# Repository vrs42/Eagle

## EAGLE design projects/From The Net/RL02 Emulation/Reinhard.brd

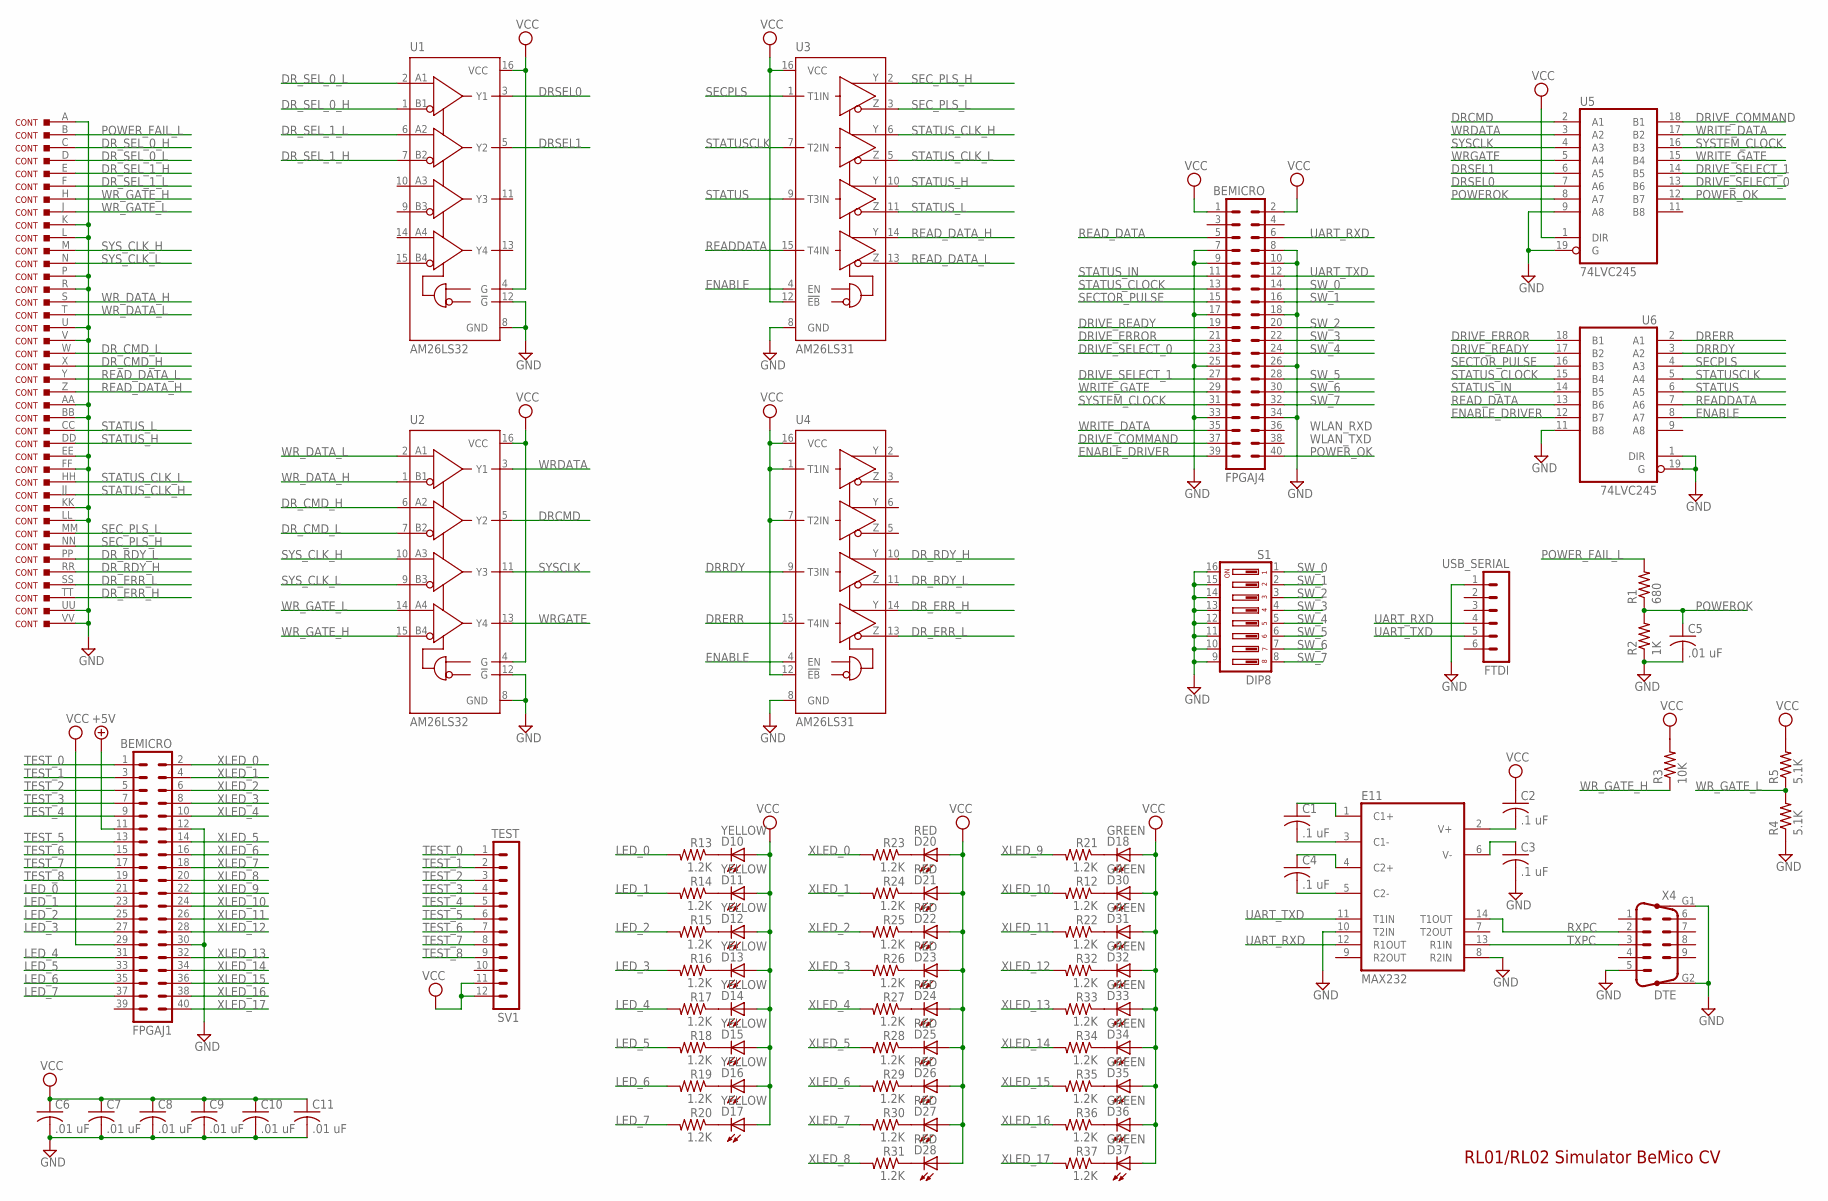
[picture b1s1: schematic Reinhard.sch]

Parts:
C1, C2, C3, C4: .1 uF; C050-025X075
C5, C6, C7, C8, C9, C10, C11: .01 uF; C050-025X075
CONT: DEC40PINSV; DEC40PINV
D10, D11, D12, D13, D14, D15, D16, D17: YELLOW; LED3MM
D18, D30, D31, D32, D33, D34, D35, D36, D37: GREEN; LED3MM
D20, D21, D22, D23, D24, D25, D26, D27, D28: RED; LED3MM
E11: MAX232; DIL16
FPGAJ1, FPGAJ4: BEMICRO; MA20-2
FTDI: USB_SERIAL; MA06-1
R1: 680; 0207/10
R2: 1K; 0207/10
R3: 10K; 0207/10
R4, R5: 5.1K; 0207/10
R12, R13, R14, R15, R16, R17, R18, R19, R20, R21, R22, R23, R24, R25, R26, R27, R28, R29, R30, R31, R32, R33, R34, R35, R36, R37: 1.2K; 0207/10
S1: DIP8; DIP08YL
SV1: TEST; MA12-1
U1, U2: AM26LS32; DIL16
U3, U4: AM26LS31; DIL16
U5, U6: 74LVC245; DIL20
X4: DTE; M09HP

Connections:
+5V: FPGAJ1.11
DRCMD: U2.5 (Y2), U5.2 (A1)
DRERR: U4.15 (T4IN), U6.2 (A1)
DRIVE_COMMAND: FPGAJ4.37, U5.18 (B1)
DRIVE_ERROR: FPGAJ4.21, U6.18 (B1)
DRIVE_READY: FPGAJ4.19, U6.17 (B2)
DRIVE_SELECT_0: FPGAJ4.23, U5.13 (B6)
DRIVE_SELECT_1: FPGAJ4.27, U5.14 (B5)
DRRDY: U4.9 (T3IN), U6.3 (A2)
DRSEL0: U1.3 (Y1), U5.7 (A6)
DRSEL1: U1.5 (Y2), U5.6 (A5)
DR_CMD_H: CONT.X, U2.6 (A2)
DR_CMD_L: CONT.W, U2.7 (B2)
DR_ERR_H: CONT.TT, U4.14 (Y4)
DR_ERR_L: CONT.SS, U4.13 (Z4)
DR_RDY_H: CONT.RR, U4.10 (Y3)
DR_RDY_L: CONT.PP, U4.11 (Z3)
DR_SEL_0_H: CONT.C, U1.1 (B1)
DR_SEL_0_L: CONT.D, U1.2 (A1)
DR_SEL_1_H: CONT.E, U1.7 (B2)
DR_SEL_1_L: CONT.F, U1.6 (A2)
ENABLE: U3.4 (EN), U4.4 (EN), U6.8 (A7)
ENABLE_DRIVER: FPGAJ4.39, U6.12 (B7)
GND: C3.2, C5.2, C6.2, C7.2, C8.2, C9.2, C10.2, C11.2, CONT.A, CONT.AA, CONT.BB, CONT.EE, CONT.FF, CONT.K, CONT.KK, CONT.L, CONT.LL, CONT.P, CONT.R, CONT.U, CONT.UU, CONT.V, CONT.VV, E11.8 (R2IN), E11.10 (T2IN), E11.15 (GND), FPGAJ1.12, FPGAJ1.30, FPGAJ4.7, FPGAJ4.8, FPGAJ4.9, FPGAJ4.10, FPGAJ4.17, FPGAJ4.18, FPGAJ4.25, FPGAJ4.26, FPGAJ4.33, FPGAJ4.34, FTDI.1, R2.1, R4.1, S1.9, S1.10, S1.11, S1.12, S1.13, S1.14, S1.15, S1.16, U1.8 (GND), U1.12 (!G), U2.8 (GND), U2.12 (!G), U3.8 (GND), U4.8 (GND), U5.9 (A8), U5.10 (GND), U5.19 (G), U6.1 (DIR), U6.10 (GND), U6.11 (B8), U6.19 (G), X4.5, X4.G1, X4.G2
LED_0: FPGAJ1.21, R13.2
LED_1: FPGAJ1.23, R14.2
LED_2: FPGAJ1.25, R15.2
LED_3: FPGAJ1.27, R16.2
LED_4: FPGAJ1.31, R17.2
LED_5: FPGAJ1.33, R18.2
LED_6: FPGAJ1.35, R19.2
LED_7: FPGAJ1.37, R20.2
unnamed: C1.2, E11.3 (C1-)
unnamed: C1.1, E11.1 (C1+)
unnamed: C4.1, E11.4 (C2+)
unnamed: C4.2, E11.5 (C2-)
unnamed: C3.1, E11.6 (V-)
unnamed: C2.2, E11.2 (V+)
unnamed: D30.K (C), R12.1
unnamed: D31.K (C), R22.1
unnamed: D32.K (C), R32.1
unnamed: D33.K (C), R33.1
unnamed: D34.K (C), R34.1
unnamed: D35.K (C), R35.1
unnamed: D36.K (C), R36.1
unnamed: D37.K (C), R37.1
unnamed: D10.K (C), R13.1
unnamed: D11.K (C), R14.1
unnamed: D12.K (C), R15.1
unnamed: D13.K (C), R16.1
unnamed: D14.K (C), R17.1
unnamed: D15.K (C), R18.1
unnamed: D16.K (C), R19.1
unnamed: D17.K (C), R20.1
unnamed: D18.K (C), R21.1
unnamed: D20.K (C), R23.1
unnamed: D21.K (C), R24.1
unnamed: D22.K (C), R25.1
unnamed: D23.K (C), R26.1
unnamed: D24.K (C), R27.1
unnamed: D25.K (C), R28.1
unnamed: D26.K (C), R29.1
unnamed: D27.K (C), R30.1
unnamed: D28.K (C), R31.1
POWEROK: C5.1, R1.1, R2.2, U5.8 (A7)
POWER_FAIL_L: CONT.B, R1.2
POWER_OK: FPGAJ4.40, U5.12 (B7)
READDATA: U3.15 (T4IN), U6.7 (A6)
READ_DATA: FPGAJ4.5, U6.13 (B6)
READ_DATA_H: CONT.Z, U3.14 (Y4)
READ_DATA_L: CONT.Y, U3.13 (Z4)
RXPC: E11.14 (T1OUT), X4.2
SECPLS: U3.1 (T1IN), U6.4 (A3)
SECTOR_PULSE: FPGAJ4.15, U6.16 (B3)
SEC_PLS_H: CONT.NN, U3.2 (Y1)
SEC_PLS_L: CONT.MM, U3.3 (Z1)
STATUS: U3.9 (T3IN), U6.6 (A5)
STATUSCLK: U3.7 (T2IN), U6.5 (A4)
STATUS_CLK_H: CONT.JJ, U3.6 (Y2)
STATUS_CLK_L: CONT.HH, U3.5 (Z2)
STATUS_CLOCK: FPGAJ4.13, U6.15 (B4)
STATUS_H: CONT.DD, U3.10 (Y3)
STATUS_IN: FPGAJ4.11, U6.14 (B5)
STATUS_L: CONT.CC, U3.11 (Z3)
SW_0: FPGAJ4.14, S1.1
SW_1: FPGAJ4.16, S1.2
SW_2: FPGAJ4.20, S1.3
SW_3: FPGAJ4.22, S1.4
SW_4: FPGAJ4.24, S1.5
SW_5: FPGAJ4.28, S1.6
SW_6: FPGAJ4.30, S1.7
SW_7: FPGAJ4.32, S1.8
SYSCLK: U2.11 (Y3), U5.4 (A3)
SYSTEM_CLOCK: FPGAJ4.31, U5.16 (B3)
SYS_CLK_H: CONT.M, U2.10 (A3)
SYS_CLK_L: CONT.N, U2.9 (B3)
TEST_0: FPGAJ1.1, SV1.1
TEST_1: FPGAJ1.3, SV1.2
TEST_2: FPGAJ1.5, SV1.3
TEST_3: FPGAJ1.7, SV1.4
TEST_4: FPGAJ1.9, SV1.5
TEST_5: FPGAJ1.13, SV1.6
TEST_6: FPGAJ1.15, SV1.7
TEST_7: FPGAJ1.17, SV1.8
TEST_8: FPGAJ1.19, SV1.9
TXPC: E11.13 (R1IN), X4.3
UART_RXD: E11.12 (R1OUT), FPGAJ4.6, FTDI.4
UART_TXD: E11.11 (T1IN), FPGAJ4.12, FTDI.5
VCC: C2.1, C6.1, C7.1, C8.1, C9.1, C10.1, C11.1, D10.A, D11.A, D12.A, D13.A, D14.A, D15.A, D16.A, D17.A, D18.A, D20.A, D21.A, D22.A, D23.A, D24.A, D25.A, D26.A, D27.A, D28.A, D30.A, D31.A, D32.A, D33.A, D34.A, D35.A, D36.A, D37.A, E11.16 (VCC), FPGAJ1.29, FPGAJ4.1, FPGAJ4.2, R3.2, R5.2, SV1.11, SV1.12, U1.4 (G), U1.16 (VCC), U2.4 (G), U2.16 (VCC), U3.12 (!EB), U3.16 (VCC), U4.1 (T1IN), U4.7 (T2IN), U4.12 (!EB), U4.16 (VCC), U5.1 (DIR), U5.20 (VCC), U6.20 (VCC)
WRDATA: U2.3 (Y1), U5.3 (A2)
WRGATE: U2.13 (Y4), U5.5 (A4)
WRITE_DATA: FPGAJ4.35, U5.17 (B2)
WRITE_GATE: FPGAJ4.29, U5.15 (B4)
WR_DATA_H: CONT.S, U2.1 (B1)
WR_DATA_L: CONT.T, U2.2 (A1)
WR_GATE_H: CONT.H, R3.1, U2.15 (B4)
WR_GATE_L: CONT.J, R4.2, R5.1, U2.14 (A4)
XLED_0: FPGAJ1.2, R23.2
XLED_1: FPGAJ1.4, R24.2
XLED_2: FPGAJ1.6, R25.2
XLED_3: FPGAJ1.8, R26.2
XLED_4: FPGAJ1.10, R27.2
XLED_5: FPGAJ1.14, R28.2
XLED_6: FPGAJ1.16, R29.2
XLED_7: FPGAJ1.18, R30.2
XLED_8: FPGAJ1.20, R31.2
XLED_9: FPGAJ1.22, R21.2
XLED_10: FPGAJ1.24, R12.2
XLED_11: FPGAJ1.26, R22.2
XLED_12: FPGAJ1.28, R32.2
XLED_13: FPGAJ1.32, R33.2
XLED_14: FPGAJ1.34, R34.2
XLED_15: FPGAJ1.36, R35.2
XLED_16: FPGAJ1.38, R36.2
XLED_17: FPGAJ1.40, R37.2

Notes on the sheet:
WLAN_RXD
WLAN_TXD
RL01/RL02 Simulator BeMico CV

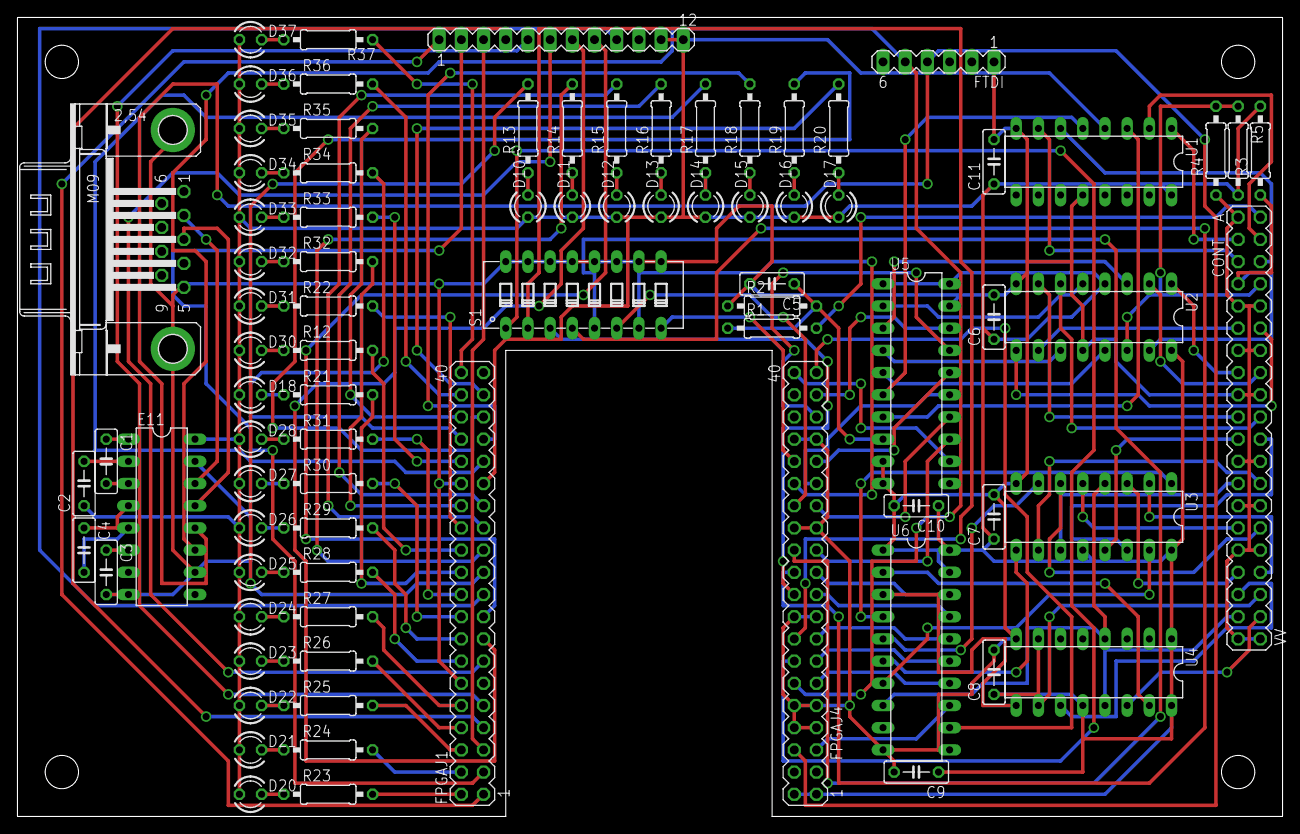
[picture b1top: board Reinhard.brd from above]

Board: 2 copper layers, 144.8 x 91.4 mm, 82 parts (0 on the bottom side), 134 nets.

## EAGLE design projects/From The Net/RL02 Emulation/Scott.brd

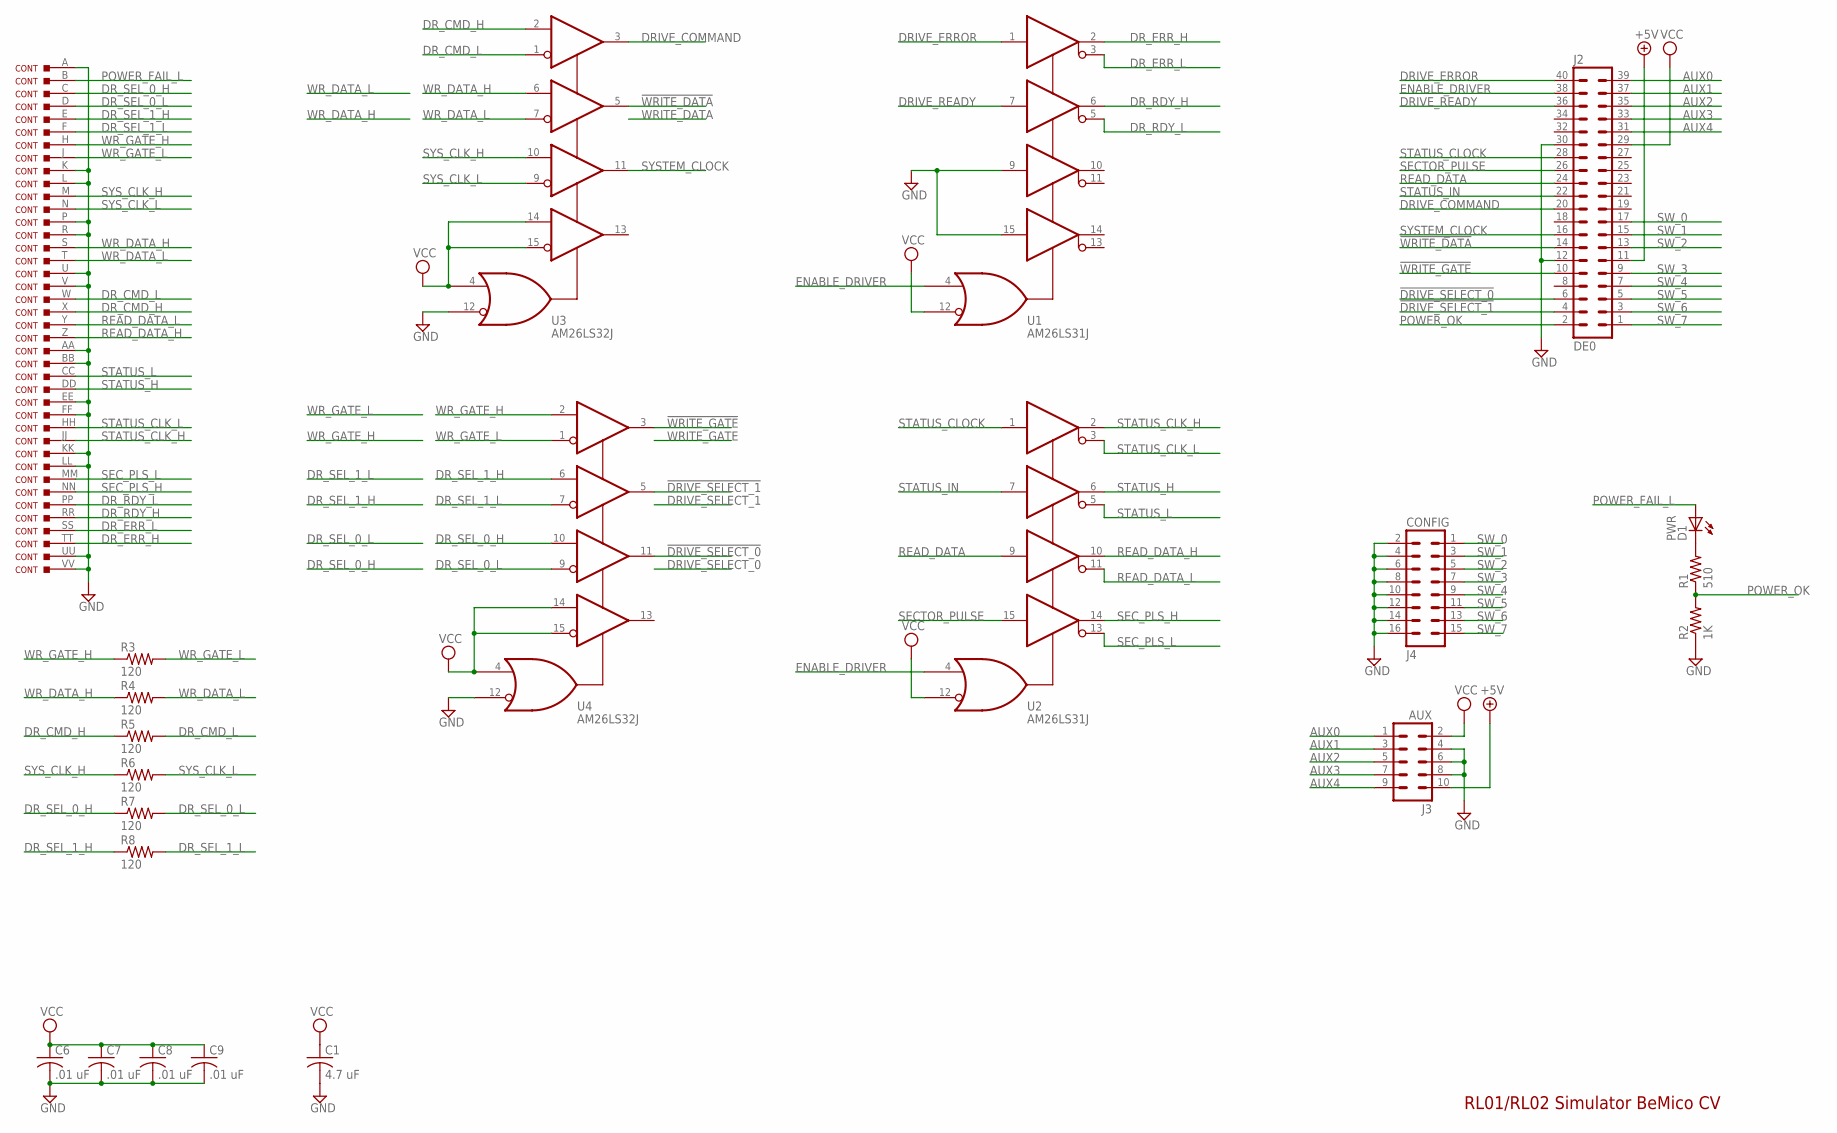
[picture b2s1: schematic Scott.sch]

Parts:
C1: 4.7 uF; C1210K
C6, C7, C8, C9: .01 uF; C0805
CONT: DEC40PINSV; DEC40PINV
D1: PWR; SML0805
J2: DE0; MA20-2
J3: AUX; MA05-2
J4: CONFIG; MA08-2
R1: 510; M0805
R2: 1K; M0805
R3, R4, R5, R6, R7, R8: 120; 0204V
U1, U2: AM26LS31J; SO16
U3, U4: AM26LS32J; SO16

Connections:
!DRIVE_SELECT_0: J2.6, U4.11 (Y3)
!DRIVE_SELECT_1: J2.4, U4.5 (Y2)
!WRITE_DATA: J2.14, U3.5 (Y2)
!WRITE_GATE: J2.10, U4.3 (Y1)
+5V: J2.11, J3.10
AUX0: J2.39, J3.1
AUX1: J2.37, J3.3
AUX2: J2.35, J3.5
AUX3: J2.33, J3.7
AUX4: J2.31, J3.9
DRIVE_COMMAND: J2.20, U3.3 (Y1)
DRIVE_ERROR: J2.40, U1.1 (A1)
DRIVE_READY: J2.36, U1.7 (A2)
DR_CMD_H: CONT.X, R5.1, U3.2 (P1)
DR_CMD_L: CONT.W, R5.2, U3.1 (N1)
DR_ERR_H: CONT.TT, U1.2 (Y1)
DR_ERR_L: CONT.SS, U1.3 (Z1)
DR_RDY_H: CONT.RR, U1.6 (Y2)
DR_RDY_L: CONT.PP, U1.5 (Z2)
DR_SEL_0_H: CONT.C, R7.1, U4.10 (P3)
DR_SEL_0_L: CONT.D, R7.2, U4.9 (N3)
DR_SEL_1_H: CONT.E, R8.1, U4.6 (P2)
DR_SEL_1_L: CONT.F, R8.2, U4.7 (N2)
ENABLE_DRIVER: J2.38, U1.4 (G), U2.4 (G)
GND: C1.2, C6.2, C7.2, C8.2, C9.2, CONT.A, CONT.AA, CONT.BB, CONT.EE, CONT.FF, CONT.K, CONT.KK, CONT.L, CONT.LL, CONT.P, CONT.R, CONT.U, CONT.UU, CONT.V, CONT.VV, J2.12, J2.30, J3.4, J3.6, J3.8, J4.2, J4.4, J4.6, J4.8, J4.10, J4.12, J4.14, J4.16, R2.1, U1.8 (GND), U1.9 (A3), U1.15 (A4), U2.8 (GND), U3.8 (GND), U3.12 (!G), U4.8 (GND), U4.12 (!G)
unnamed: D1.C, R1.2
POWER_FAIL_L: CONT.B, D1.A
POWER_OK: J2.2, R1.1, R2.2
READ_DATA: J2.24, U2.9 (A3)
READ_DATA_H: CONT.Z, U2.10 (Y3)
READ_DATA_L: CONT.Y, U2.11 (Z3)
SECTOR_PULSE: J2.26, U2.15 (A4)
SEC_PLS_H: CONT.NN, U2.14 (Y4)
SEC_PLS_L: CONT.MM, U2.13 (Z4)
STATUS_CLK_H: CONT.JJ, U2.2 (Y1)
STATUS_CLK_L: CONT.HH, U2.3 (Z1)
STATUS_CLOCK: J2.28, U2.1 (A1)
STATUS_H: CONT.DD, U2.6 (Y2)
STATUS_IN: J2.22, U2.7 (A2)
STATUS_L: CONT.CC, U2.5 (Z2)
SW_0: J2.17, J4.1
SW_1: J2.15, J4.3
SW_2: J2.13, J4.5
SW_3: J2.9, J4.7
SW_4: J2.7, J4.9
SW_5: J2.5, J4.11
SW_6: J2.3, J4.13
SW_7: J2.1, J4.15
SYSTEM_CLOCK: J2.16, U3.11 (Y3)
SYS_CLK_H: CONT.M, R6.1, U3.10 (P3)
SYS_CLK_L: CONT.N, R6.2, U3.9 (N3)
VCC: C1.1, C6.1, C7.1, C8.1, C9.1, J2.29, J3.2, U1.12 (!G), U1.16 (VCC), U2.12 (!G), U2.16 (VCC), U3.4 (G), U3.14 (P4), U3.15 (N4), U3.16 (VCC), U4.4 (G), U4.14 (P4), U4.15 (N4), U4.16 (VCC)
WR_DATA_H: CONT.S, R4.1, U3.6 (P2)
WR_DATA_L: CONT.T, R4.2, U3.7 (N2)
WR_GATE_H: CONT.H, R3.1, U4.2 (P1)
WR_GATE_L: CONT.J, R3.2, U4.1 (N1)

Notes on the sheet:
RL01/RL02 Simulator BeMico CV

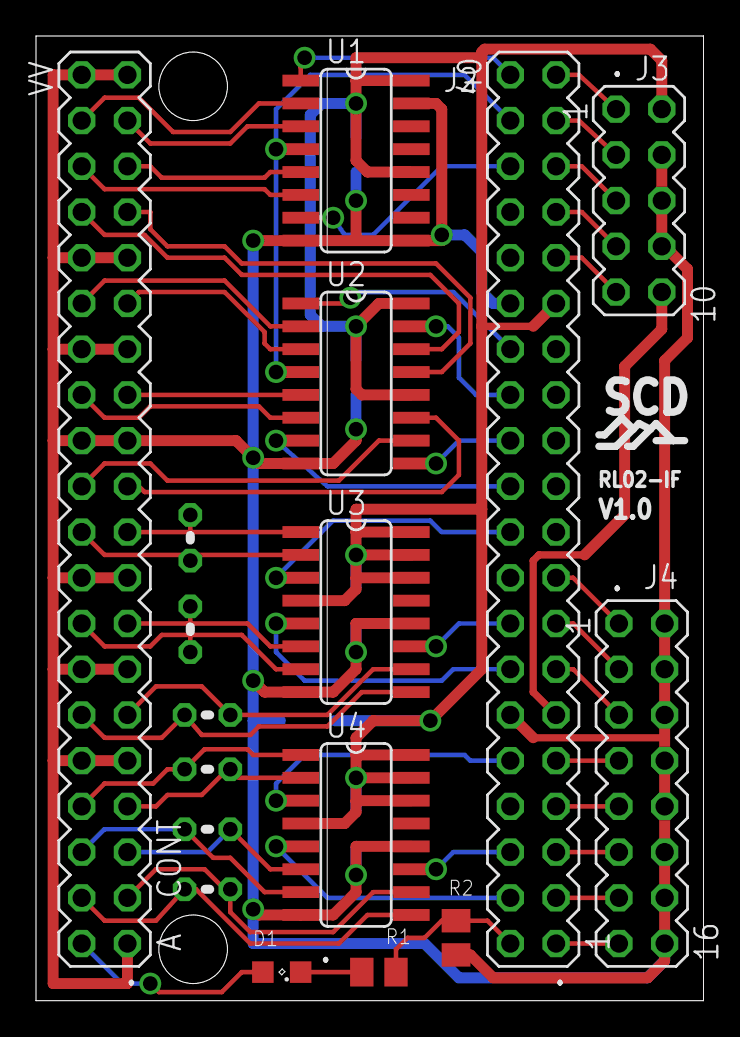
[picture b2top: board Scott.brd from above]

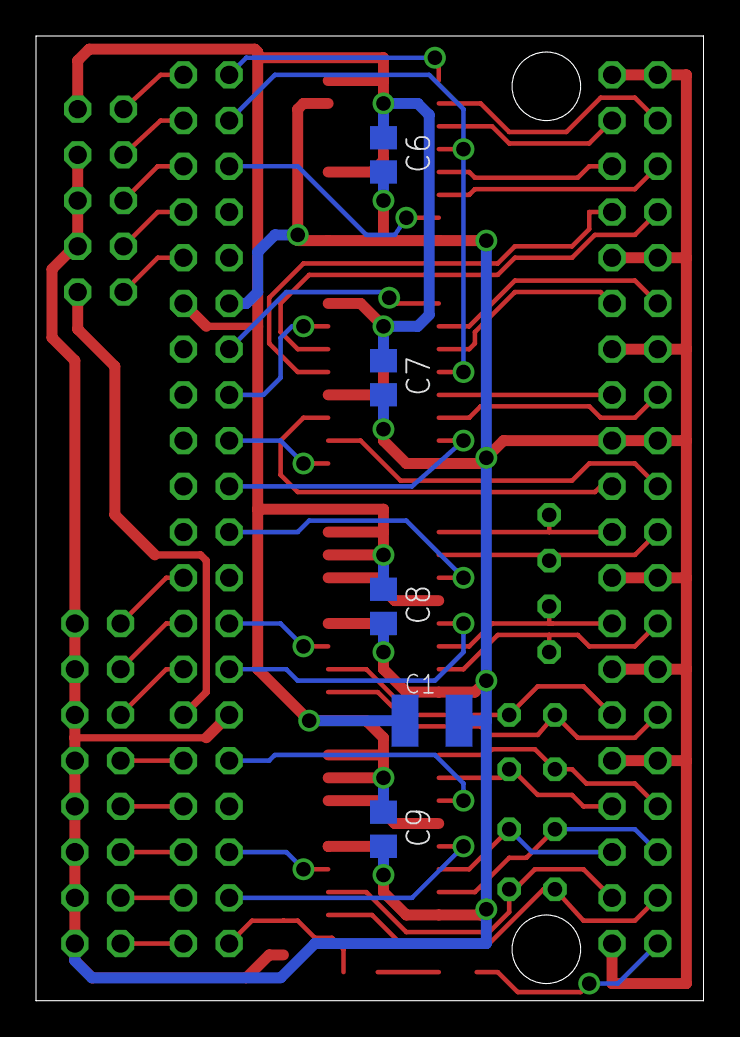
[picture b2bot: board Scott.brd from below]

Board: 2 copper layers, 37.1 x 53.6 mm, 22 parts (5 on the bottom side), 56 nets.

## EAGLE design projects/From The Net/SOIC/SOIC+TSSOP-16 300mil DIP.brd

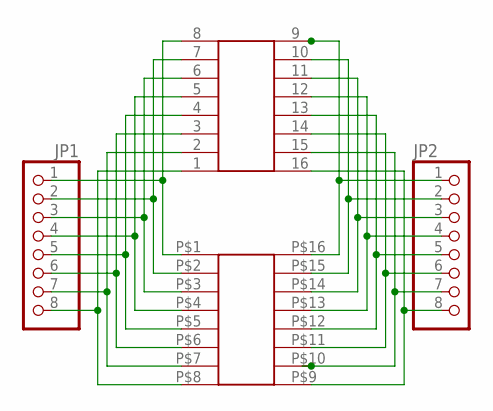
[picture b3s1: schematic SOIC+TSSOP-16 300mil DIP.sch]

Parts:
JP1, JP2: PINHD-1X8; 1X08
U$1: SMD-16SOIC; SO-16NMW
U$2: SMD-16TSSOP; TSSOP-16NM

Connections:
unnamed: JP1.1, U$1.P$1, U$2.8
unnamed: JP1.2, U$1.P$2, U$2.7
unnamed: JP1.3, U$1.P$3, U$2.6
unnamed: JP1.4, U$1.P$4, U$2.5
unnamed: JP1.5, U$1.P$5, U$2.4
unnamed: JP1.6, U$1.P$6, U$2.3
unnamed: JP1.7, U$1.P$7, U$2.2
unnamed: JP1.8, U$1.P$8, U$2.1
unnamed: JP2.1, U$1.P$16, U$2.9
unnamed: JP2.2, U$1.P$15, U$2.10
unnamed: JP2.3, U$1.P$14, U$2.11
unnamed: JP2.4, U$1.P$13, U$2.12
unnamed: JP2.5, U$1.P$12, U$2.13
unnamed: JP2.6, U$1.P$11, U$2.14
unnamed: JP2.7, U$1.P$10, U$2.15
unnamed: JP2.8, U$1.P$9, U$2.16

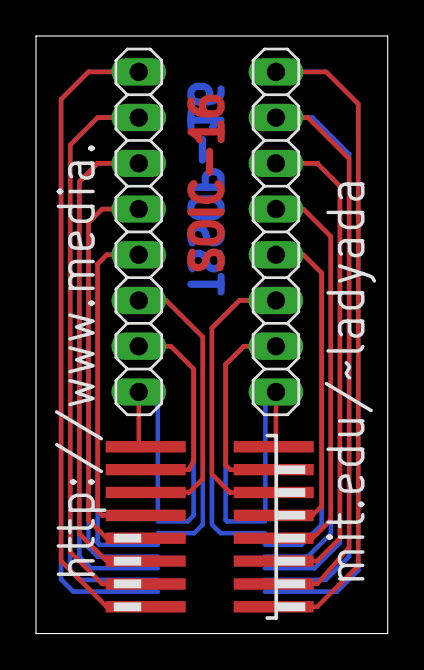
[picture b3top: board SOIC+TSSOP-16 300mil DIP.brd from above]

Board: 2 copper layers, 19.5 x 33.2 mm, 4 parts (1 on the bottom side), 16 nets.

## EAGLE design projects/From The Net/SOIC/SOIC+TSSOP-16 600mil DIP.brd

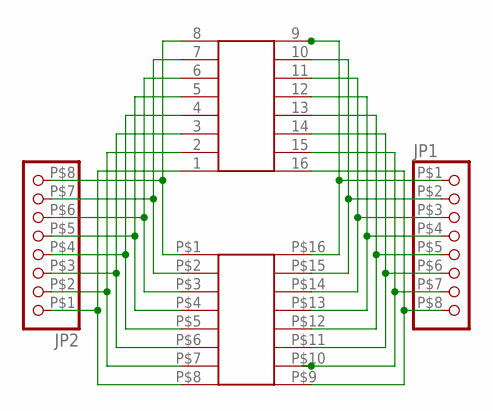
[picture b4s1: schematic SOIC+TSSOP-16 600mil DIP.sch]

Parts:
JP1, JP2: PINHD-1X8THIN; HEADER1X8
U$1: SMD-16SOIC; SO-16NMW
U$2: SMD-16TSSOP; TSSOP-16NM

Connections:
unnamed: JP2.P$8 (8), U$1.P$1, U$2.8
unnamed: JP2.P$7 (7), U$1.P$2, U$2.7
unnamed: JP2.P$6 (6), U$1.P$3, U$2.6
unnamed: JP2.P$5 (5), U$1.P$4, U$2.5
unnamed: JP2.P$4 (4), U$1.P$5, U$2.4
unnamed: JP2.P$3 (3), U$1.P$6, U$2.3
unnamed: JP2.P$2 (2), U$1.P$7, U$2.2
unnamed: JP2.P$1 (1), U$1.P$8, U$2.1
unnamed: JP1.P$1 (1), U$1.P$16, U$2.9
unnamed: JP1.P$2 (2), U$1.P$15, U$2.10
unnamed: JP1.P$3 (3), U$1.P$14, U$2.11
unnamed: JP1.P$4 (4), U$1.P$13, U$2.12
unnamed: JP1.P$5 (5), U$1.P$12, U$2.13
unnamed: JP1.P$6 (6), U$1.P$11, U$2.14
unnamed: JP1.P$7 (7), U$1.P$10, U$2.15
unnamed: JP1.P$8 (8), U$1.P$9, U$2.16

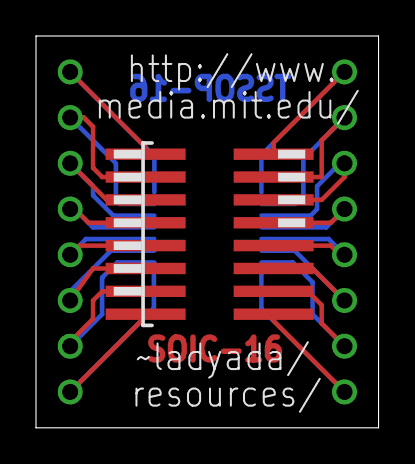
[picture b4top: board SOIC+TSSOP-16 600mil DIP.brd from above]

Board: 2 copper layers, 19.0 x 21.8 mm, 4 parts (1 on the bottom side), 16 nets.

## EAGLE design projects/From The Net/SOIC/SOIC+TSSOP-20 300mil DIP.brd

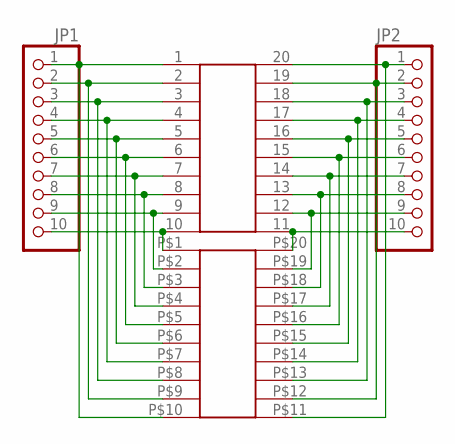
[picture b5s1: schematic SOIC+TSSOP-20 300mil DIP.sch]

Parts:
JP1, JP2: PINHD-1X10; 1X10
U$1: SMD-20TSSOP; TSSOP-20NM
U$2: SMD-20SOIC; SO-20NMW

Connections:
unnamed: JP1.1, U$1.1, U$2.P$10
unnamed: JP1.2, U$1.2, U$2.P$9
unnamed: JP1.3, U$1.3, U$2.P$8
unnamed: JP1.4, U$1.4, U$2.P$7
unnamed: JP1.5, U$1.5, U$2.P$6
unnamed: JP1.6, U$1.6, U$2.P$5
unnamed: JP1.7, U$1.7, U$2.P$4
unnamed: JP1.8, U$1.8, U$2.P$3
unnamed: JP1.9, U$1.9, U$2.P$2
unnamed: JP1.10, U$1.10, U$2.P$1
unnamed: JP2.1, U$1.20, U$2.P$11
unnamed: JP2.2, U$1.19, U$2.P$12
unnamed: JP2.3, U$1.18, U$2.P$13
unnamed: JP2.5, U$1.16, U$2.P$15
unnamed: JP2.4, U$1.17, U$2.P$14
unnamed: JP2.6, U$1.15, U$2.P$16
unnamed: JP2.7, U$1.14, U$2.P$17
unnamed: JP2.8, U$1.13, U$2.P$18
unnamed: JP2.9, U$1.12, U$2.P$19
unnamed: JP2.10, U$1.11, U$2.P$20

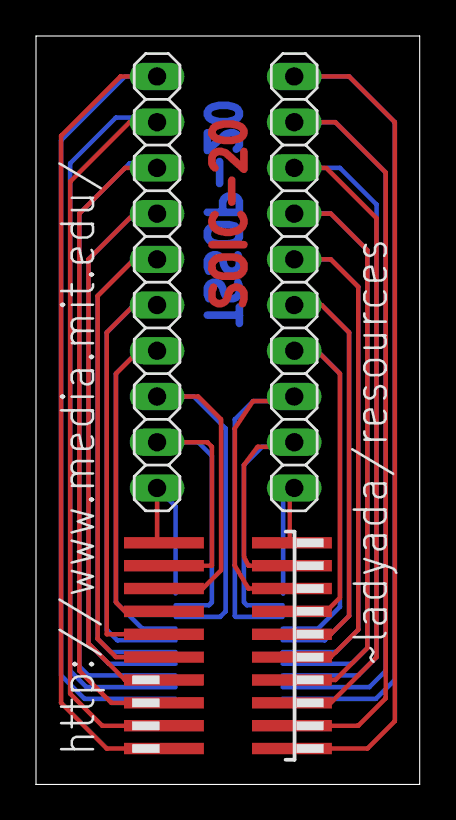
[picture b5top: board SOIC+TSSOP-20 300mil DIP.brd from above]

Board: 2 copper layers, 21.3 x 41.6 mm, 4 parts (1 on the bottom side), 20 nets.

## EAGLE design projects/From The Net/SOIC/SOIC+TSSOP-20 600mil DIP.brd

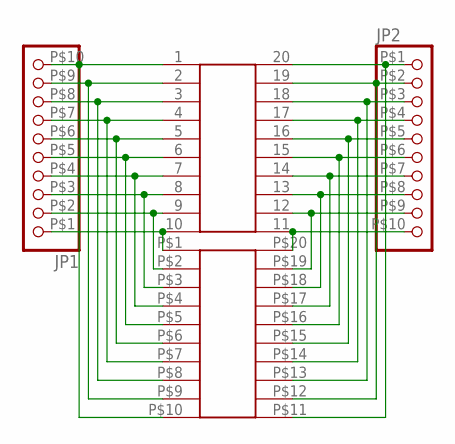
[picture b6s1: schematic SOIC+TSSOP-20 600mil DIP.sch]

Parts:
JP1, JP2: PINHD-1X10THIN; HEADER1X10
U$1: SMD-20TSSOP; TSSOP-20NM
U$2: SMD-20SOIC; SO-20NMW

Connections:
unnamed: JP1.P$10 (10), U$1.1, U$2.P$10
unnamed: JP1.P$9 (9), U$1.2, U$2.P$9
unnamed: JP1.P$8 (8), U$1.3, U$2.P$8
unnamed: JP1.P$7 (7), U$1.4, U$2.P$7
unnamed: JP1.P$6 (6), U$1.5, U$2.P$6
unnamed: JP1.P$5 (5), U$1.6, U$2.P$5
unnamed: JP1.P$4 (4), U$1.7, U$2.P$4
unnamed: JP1.P$3 (3), U$1.8, U$2.P$3
unnamed: JP1.P$2 (2), U$1.9, U$2.P$2
unnamed: JP1.P$1 (1), U$1.10, U$2.P$1
unnamed: JP2.P$1 (1), U$1.20, U$2.P$11
unnamed: JP2.P$2 (2), U$1.19, U$2.P$12
unnamed: JP2.P$3 (3), U$1.18, U$2.P$13
unnamed: JP2.P$5 (5), U$1.16, U$2.P$15
unnamed: JP2.P$4 (4), U$1.17, U$2.P$14
unnamed: JP2.P$6 (6), U$1.15, U$2.P$16
unnamed: JP2.P$7 (7), U$1.14, U$2.P$17
unnamed: JP2.P$8 (8), U$1.13, U$2.P$18
unnamed: JP2.P$9 (9), U$1.12, U$2.P$19
unnamed: JP2.P$10 (10), U$1.11, U$2.P$20

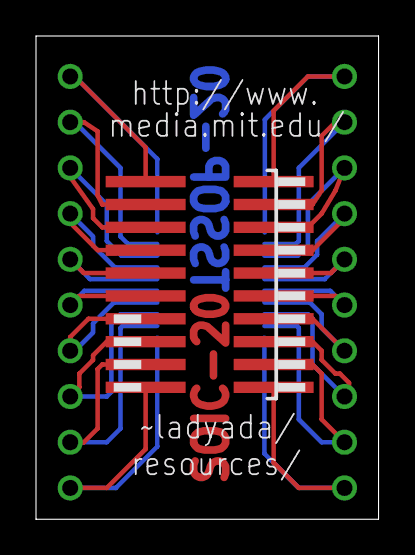
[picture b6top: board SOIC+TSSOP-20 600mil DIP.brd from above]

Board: 2 copper layers, 19.0 x 26.8 mm, 4 parts (1 on the bottom side), 20 nets.

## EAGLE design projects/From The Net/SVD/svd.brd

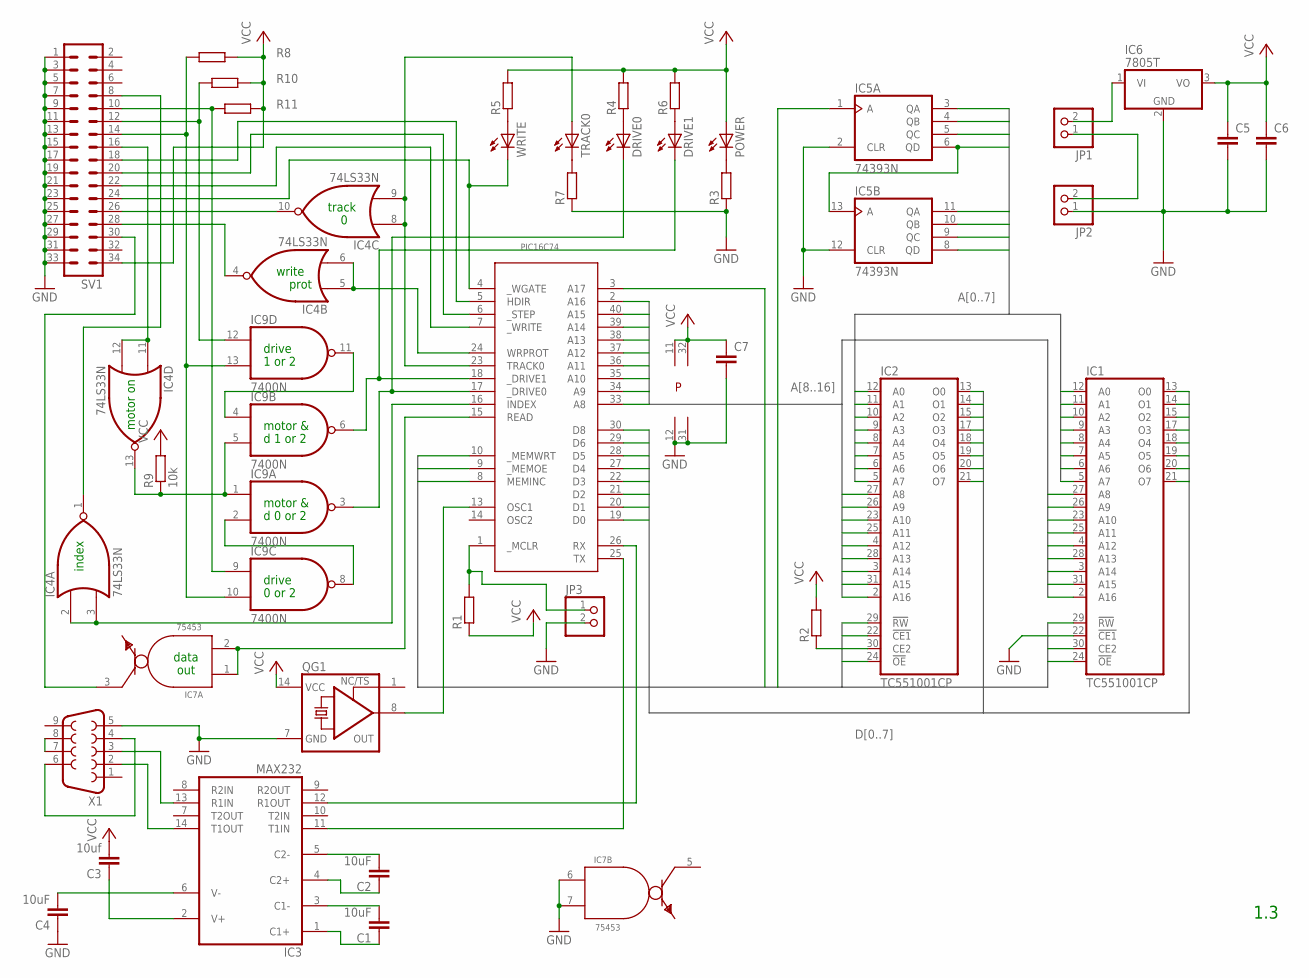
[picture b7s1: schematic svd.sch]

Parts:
C1, C2, C4: 10uF; C2.5-5
C3: 10uf; C2.5-5
C5, C6: C5/5; C5B5
C7: C2,5-3; C2.5-3
DRIVE0, DRIVE1: LED3MM
IC1, IC2: TC551001CP; DIL32
IC3: MAX232; DIL16
IC4: 74LS33N; DIL14
IC5: 74393N; DIL14
IC6: 7805T; TO220H
IC7: 75453; DIL08
IC9: 7400N; DIL14
JP1, JP2, JP3: PINHD-1X2; 1X02
PIC16C74: SVD-PIC16C74; DIL40
POWER: LED3MM
QG1: XO-14; DIL14S
R1, R2, R3, R4, R5, R6, R7, R8, R10, R11: R-EU_0204/5; 0204/5
R9: 10k; 0204/5
SV1: ML34
TRACK0: LED3MM
WRITE: LED3MM
X1: F09HP

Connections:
!OE: IC1.24 (!OE), IC2.24 (!OE), PIC16C74.9 (_MEMOE)
!WE: IC1.29 (!RW), IC2.29 (!RW), PIC16C74.10 (_MEMWRT)
A0: IC1.12 (A0), IC2.12 (A0), IC5.3 (QA)
A1: IC1.11 (A1), IC2.11 (A1), IC5.4 (QB)
A2: IC1.10 (A2), IC2.10 (A2), IC5.5 (QC)
A3: IC1.9 (A3), IC2.9 (A3), IC5.6 (QD), IC5.13 (A)
A4: IC1.8 (A4), IC2.8 (A4), IC5.11 (QA)
A5: IC1.7 (A5), IC2.7 (A5), IC5.10 (QB)
A6: IC1.6 (A6), IC2.6 (A6), IC5.9 (QC)
A7: IC1.5 (A7), IC2.5 (A7), IC5.8 (QD)
A8: IC1.27 (A8), IC2.27 (A8), PIC16C74.33 (A8)
A9: IC1.26 (A9), IC2.26 (A9), PIC16C74.34 (A9)
A10: IC1.23 (A10), IC2.23 (A10), PIC16C74.35 (A10)
A11: IC1.25 (A11), IC2.25 (A11), PIC16C74.36 (A11)
A12: IC1.4 (A12), IC2.4 (A12), PIC16C74.37 (A12)
A13: IC1.28 (A13), IC2.28 (A13), PIC16C74.38 (A13)
A14: IC1.3 (A14), IC2.3 (A14), PIC16C74.39 (A14)
A15: IC1.31 (A15), IC2.31 (A15), PIC16C74.40 (A15)
A16: IC1.2 (A16), IC2.2 (A16), PIC16C74.2 (A16)
A17: IC1.30 (CE2), IC2.22 (!CE1), PIC16C74.3 (A17)
CLK: IC5.1 (A), PIC16C74.8 (MEMINC)
D0: IC1.13 (O0), IC2.13 (O0), PIC16C74.19 (D0)
D1: IC1.14 (O1), IC2.14 (O1), PIC16C74.20 (D1)
D2: IC1.15 (O2), IC2.15 (O2), PIC16C74.21 (D2)
D3: IC1.17 (O3), IC2.17 (O3), PIC16C74.22 (D3)
D4: IC1.18 (O4), IC2.18 (O4), PIC16C74.27 (D4)
D5: IC1.19 (O5), IC2.19 (O5), PIC16C74.28 (D5)
D6: IC1.20 (O6), IC2.20 (O6), PIC16C74.29 (D6)
D7: IC1.21 (O7), IC2.21 (O7), PIC16C74.30 (D8)
GND: C4.1, C5.2, C6.2, C7.2, IC1.16 (GND), IC1.22 (!CE1), IC2.16 (GND), IC3.15 (GND), IC4.7 (GND), IC5.2 (CLR), IC5.7 (GND), IC5.12 (CLR), IC6.2 (GND), IC7.4 (GND), IC7.6 (I0), IC7.7 (I1), IC9.7 (GND), JP2.1, JP3.2, PIC16C74.12 (GND), PIC16C74.31 (GND), QG1.7 (GND), R3.1, R7.1, SV1.1, SV1.3, SV1.5, SV1.7, SV1.9, SV1.11, SV1.13, SV1.15, SV1.17, SV1.19, SV1.21, SV1.23, SV1.25, SV1.27, SV1.29, SV1.31, SV1.33, X1.5
unnamed: IC2.30 (CE2), R2.1
unnamed: JP3.1, PIC16C74.1 (_MCLR), R1.2
unnamed: C1.1, IC3.1 (C1+)
unnamed: C1.2, IC3.3 (C1-)
unnamed: C2.1, IC3.4 (C2+)
unnamed: C2.2, IC3.5 (C2-)
unnamed: C3.1, IC3.2 (V+)
unnamed: PIC16C74.13 (OSC1), QG1.8 (OUT)
unnamed: IC3.12 (R1OUT), PIC16C74.26 (RX)
unnamed: DRIVE1.K (C), IC9.6 (O), PIC16C74.18 (_DRIVE1)
unnamed: IC4.11 (I0), IC4.12 (I1), SV1.16
unnamed: IC9.12 (I0), R10.1, SV1.12
unnamed: IC4.13 (O), IC9.1 (I0), IC9.5 (I1), R9.1
unnamed: IC4.1 (O), SV1.8
unnamed: PIC16C74.4 (_WGATE), SV1.24, WRITE.K (C)
unnamed: PIC16C74.7 (_WRITE), SV1.22
unnamed: IC4.10 (O), SV1.26
unnamed: X1.7, X1.8
unnamed: IC7.1 (I0), IC7.2 (I1), PIC16C74.15 (READ)
unnamed: IC9.4 (I0), IC9.11 (O)
unnamed: IC4.8 (I0), IC4.9 (I1), PIC16C74.23 (TRACK0), TRACK0.A
unnamed: DRIVE0.K (C), IC9.3 (O), PIC16C74.17 (_DRIVE0)
unnamed: IC3.11 (T1IN), PIC16C74.25 (TX)
unnamed: IC3.13 (R1IN), X1.3
unnamed: X1.4, X1.6
unnamed: IC3.14 (T1OUT), X1.2
unnamed: C4.2, IC3.6 (V-)
unnamed: IC4.2 (I0), IC4.3 (I1), PIC16C74.16 (INDEX)
unnamed: IC6.1 (VI), JP1.2
unnamed: POWER.K (C), R3.2
unnamed: DRIVE0.A, R4.1
unnamed: DRIVE1.A, R6.1
unnamed: R5.1, WRITE.A
unnamed: R7.2, TRACK0.K (C)
unnamed: JP1.1, JP2.2
unnamed: IC7.3 (O), SV1.30
unnamed: IC4.5 (I0), IC4.6 (I1), PIC16C74.24 (WRPROT)
unnamed: IC9.9 (I0), R11.1, SV1.10
unnamed: IC9.2 (I1), IC9.8 (O)
unnamed: IC4.4 (O), SV1.28
unnamed: PIC16C74.6 (_STEP), SV1.20
unnamed: PIC16C74.5 (HDIR), SV1.18
unnamed: IC9.10 (I1), IC9.13 (I1), R8.1, SV1.14
VCC: C3.2, C5.1, C6.1, C7.1, IC1.32 (VCC), IC2.32 (VCC), IC3.16 (VCC), IC4.14 (VCC), IC5.14 (VCC), IC6.3 (VO), IC7.8 (VCC), IC9.14 (VCC), PIC16C74.11 (VCC), PIC16C74.32 (VCC), POWER.A, QG1.14 (VCC), R1.1, R2.2, R4.2, R5.2, R6.2, R8.2, R9.2, R10.2, R11.2, SV1.34

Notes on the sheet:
1.3
motor on
index
data
out
write
prot
track
drive
motor &
1 or 2
d 1 or 2
d 0 or 2
0 or 2

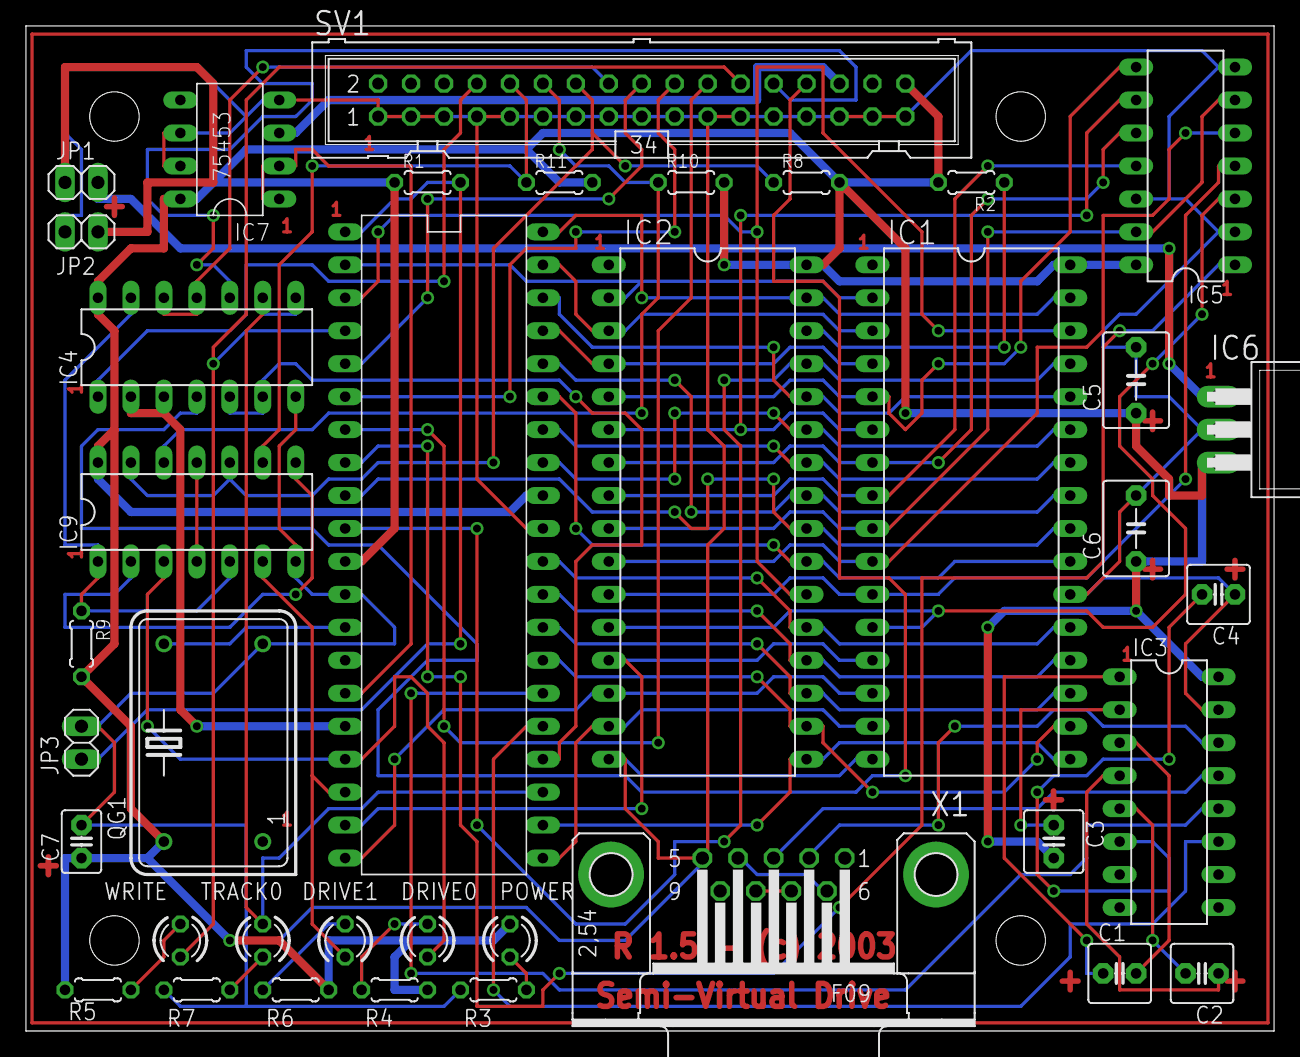
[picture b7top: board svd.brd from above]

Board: 2 copper layers, 96.2 x 77.5 mm, 38 parts (0 on the bottom side), 74 nets.

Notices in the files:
projects/From The Net/SVD/svd.brd:
R 1.5 - (c) 2003
